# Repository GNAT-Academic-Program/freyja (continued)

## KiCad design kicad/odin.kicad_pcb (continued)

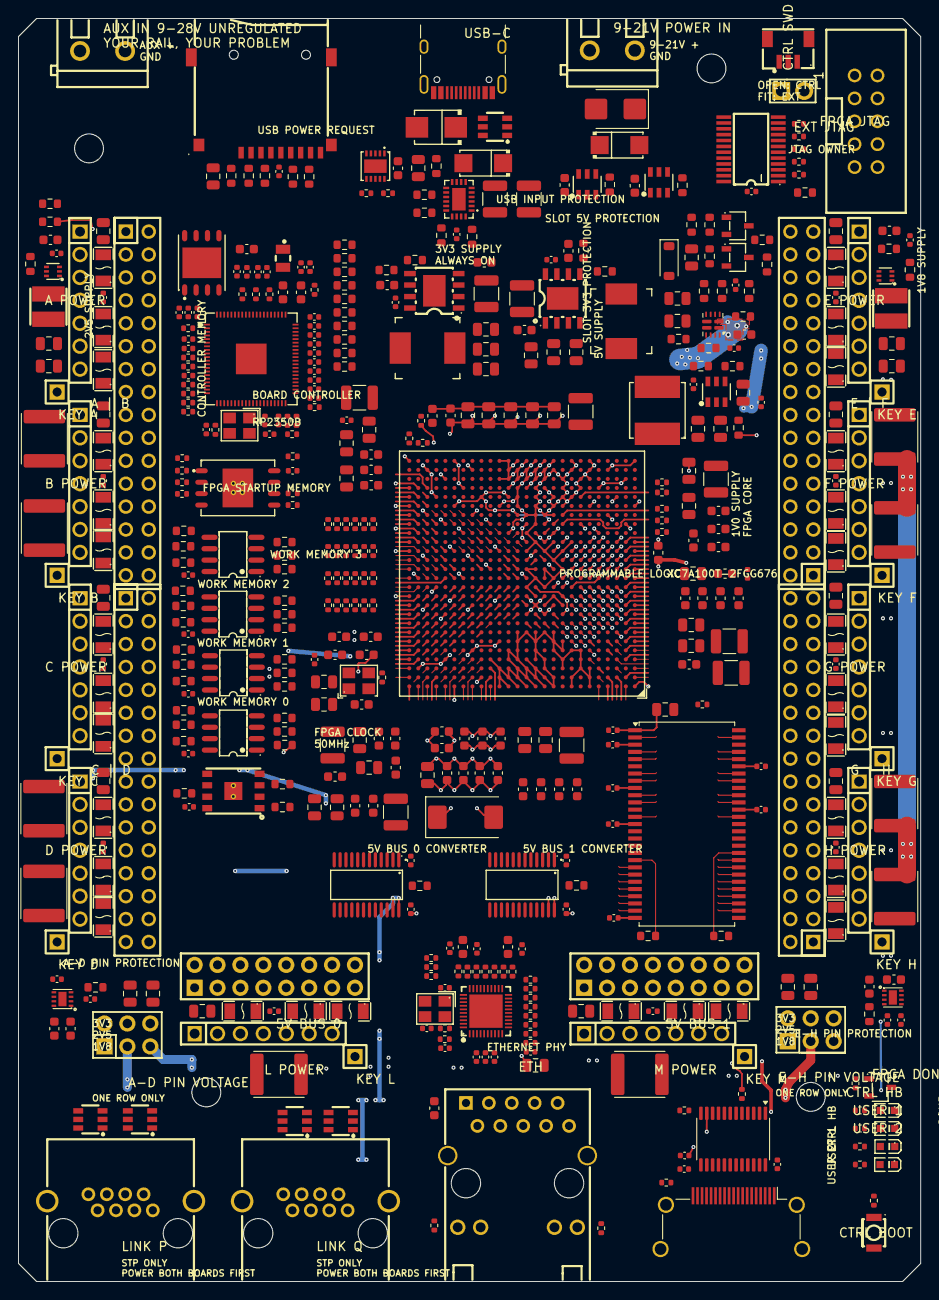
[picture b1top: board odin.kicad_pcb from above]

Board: 8 copper layers, 100.0 x 140.0 mm, 524 parts (0 on the bottom side), 498 nets.

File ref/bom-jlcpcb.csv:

Comment,Designator,Footprint,LCSC Part
100nF,"C111,C112,C113,C114,C115,C116,C117,C118,C119,C120,C121,C122,C123,C124,C125,C126,C127,C128,C129,C135,C136,C138,C139,C140,C141,C142,C144,C146,C148,C150,C152,C154,C156,C158,C160,C162,C188,C193,C200,C203,C225,C226,C227,C228,C229,C230,C232,C233,C234,C236,C238,C239,C240,C241,C246,C247,C248,C249,C250,C251,C252,C253,C254,C255,C256,C258,C259,C262,C263,C271,C274,C277,C278,C285,C286,C328",C_0402_1005Metric,C1525
4.7uF,"C130,C131,C132,C242,C268,C269",C_0603_1608Metric,C277476
15pF,"C133,C134",C_0402_1005Metric,
1uF 25V,C137,C_0603_1608Metric,C29936
10uF,"C143,C145,C147,C149,C151,C153,C155,C157,C159,C161,C235,C257,C260,C261,C279",C_0805_2012Metric,C15850
22uF,"C163,C164,C165,C166,C189,C190,C191,C195,C196,C197,C198,C199,C201,C202,C207,C211,C212,C265,C266",C_0805_2012Metric,C86816
10nF 25V,C184,C_0402_1005Metric,
10uF 50V,"C185,C186,C192,C267",C_1210_3225Metric,C77102
10uF 25V,C187,C_0805_2012Metric,C15850
1uF,"C218,C219,C220,C221,C237,C273,C276,C280,C281,C283",C_0603_1608Metric,C29936
100nF 50V,C243,C_0603_1608Metric,
18pF,"C244,C245",C_0402_1005Metric,
100nF 25V,C264,C_0402_1005Metric,C1525
1nF 50V,"C272,C275",C_0402_1005Metric,
220nF 50V,"C282,C284",C_0603_1608Metric,
330uF 6.3V T520V337M006ATE025,C301,CP_EIA-7343-31_Kemet-D,C136150
4.7uF 6.3V,"C302,C303,C304,C305,C306,C307,C320,C321,C322,C330,C331,C336,C337,C342,C343,C348,C349,C354,C355,C360,C361",C_0805_2012Metric,
0.47uF 6.3V,"C308,C309,C310,C311,C312,C313,C314,C315,C317,C318,C323,C324,C325,C326,C327,C332,C333,C334,C335,C338,C339,C340,C341,C344,C345,C346,C347,C350,C351,C352,C353,C356,C357,C358,C359,C362,C363,C364,C365",C_0603_1608Metric,
100uF 2.5V,C316,C_1210_3225Metric,
47uF 6.3V,"C319,C329,C366,C367,C368,C369,C394",C_1210_3225Metric,
F.0603.00025/P2-0603G1TS2-06T-002,"D1,D9,D10,D11",LED0603-RD_GREEN,C7496818
SS54,"D3,D4",SMA_L4.3-W2.6-LS5.2-RD,C22452
ESDA6V1BC6,D6,SOT-23-6_L2.9-W1.6-P0.95-LS2.8-BR,C495220
SMBJ12A,D7,SMB_L4.3-W3.6-LS5.3-RD,C19077565
SMBJ22A,D8,D_SMB,C151920
TPD4E1U06DBVR,"D20,D21,D22,D23",SOT-23-6_L2.9-W1.6-P0.95-LS2.8-BR_TPD4E1U06,C124691
1N4148W,D24,D_SOD-123,C81598
500mA,"F1,F3,F5,F7,F9,F11,F13,F15,F17,F19,F21,F23,F25,F27,F29,F31,F33,F35,F37,F39",F1206,C269115
1.1A,"F2,F6,F10,F14,F18,F22,F26,F30,F34,F38",F1206,C269119
1.1A 33V,"F4,F8,F12,F16,F20,F24,F28,F32,F36,F40",Fuse_TECHFUSE_SMD2018,C70150
120R 2A BLM18PG121SN1D,FB1,L_0603_1608Metric,C14709
USB-C,J1,USB_C_Receptacle_HRO_TYPE-C-31-M-12,C165948
FPGA JTAG,J2,IDC-TH_10P-P2.54_C5665,C5665
HC-PM254-8.5H-2x16PZ,"J3A,J3B,J5A,J5B",HDR-TH_32P-P2.54-V-F-R2-C16-S2.54,C22373921
2.54-2*8P female 8.5mm,"J7,J8",HDR-TH_16P-P2.54-V-F-R2-C8-S2.54,C30734
2.54-2*3P,"J19,J20",HDR-TH_6P-P2.54-V-M-R2-C3-S2.54-1,C65114
9-21V POWER IN,J50,CONN-TH_P5.00_KF301-5.0-2P,C474881
CTRL SWD,J51,CONN-SMD-3P-P1.00_BM03B-SRSS-TB-LF-SN,C160389
PZ254V-11-02P,J52,HDR-TH_2P-P2.54-V-M,C492401
B254N02-0B7P51-H85C32,"J53,J54,J55,J56,J57,J58,J62,J63,J64,J65",HDR-TH_7P-P2.54-V-F,C41426870
AUX IN 9-28V UNREGULATED,J68,CONN-TH_P5.00_KF301-5.0-2P,C474881
ETH,J70,RJ45-TH_HR911130A,C54408
LINK P,J71,RJ45-TH_R-RJ45R08P-B000,C386756
LINK Q,J72,RJ45-TH_R-RJ45R08P-B000,C386756
HDMI OUT,J73,HDMI_A_Amphenol_10029449-x01xLF_Horizontal,C427307
microSD,J74,TF-SMD_TF-01A-NPTH,C91145
3.3uH AOTA-B201610S3R3-101-T,L1,IND-SMD_L2.0-W1.6_AOTA-B201610S3R3-101-T,C42411119
10uH MWSA0603S-100MT,"L2,L3",IND-SMD_L7.0-W6.6_MWSA0603S,C132141
2.2uH SRN4018-2R2M,"L4,L5",IND-SMD_L4.0-W4.0_SNR4018,C913207
4.7uH SWPA6045S4R7MT,L7,IND-SMD_L6.0-W6.0_SWPA6045S,C78804
BOOMELE 2.54-1x40P-21mm; cut to 1P; hand/wave soldered,"MK65,MK66,MK67,MK68,MK69,MK70,MK71,MK72,MK76,MK77",HDR-TH_1P-P2.54-V-M-21MM-C51353,C51353
BSS138LT1G,"Q4,Q6,Q7",SOT-23-3_L2.9-W1.6-P1.90-LS2.8-BR,C82045
1k,"R1,R2,R3,R6,R9,R10,R12,R128,R129,R130,R132",R_0402_1005Metric,C11702
4.7k,"R4,R5,R98,R133,R135,R136,R137,R138,R139,R140,R141,R142,R143,R172,R203,R204",R_0402_1005Metric,C25900
330,R7,R_0402_1005Metric,
33,"R8,R14,R15,R16,R17,R18,R19,R20,R21,R22,R23,R24,R25,R26,R27,R28,R29,R30,R31,R32,R104,R105,R106,R107,R108,R109,R110,R111,R112,R113,R114,R115,R116,R117,R118,R119,R120,R121,R122,R123,R124,R125,R126,R127,R147,R208",R_0402_1005Metric,C25105
0,"R33,R146,R205",R_0402_1005Metric,
10k,"R34,R73,R96,R97,R152,R153,R154,R155,R156,R157,R158,R159,R160,R161,R169,R174,R175,R176,R177,R178,R179,R180,R181,R182,R183,R184,R185,R186,R187,R188,R189,R190,R191,R192,R193,R194,R195,R196,R197,R207",R_0603_1608Metric,
110k,R50,R_0603_1608Metric,
24.9k,R51,R_0603_1608Metric,
14.7k,R52,R_0603_1608Metric,
29.4k,"R54,R168",R_0603_1608Metric,
100k 0.1%,"R55,R57,R59",R_0603_1608Metric,C122538
24.9k 0.1%,R56,R_0603_1608Metric,C136967
43.2k 0.1%,R58,R_0603_1608Metric,C861404
31.6k 0.1%,R60,R_0603_1608Metric,C705766
102k 0.1%,R61,R_0603_1608Metric,C861068
49.9k 0.1%,R62,R_0603_1608Metric,C705780
3.09k 0.1%,R67,R_0603_1608Metric,C861371
10k 0.1%,R68,R_0603_1608Metric,C95204
100k,"R72,R81,R83,R91,R94,R162,R164,R166,R201",R_0603_1608Metric,
604,R74,R_0603_1608Metric,
1.15k,R75,R_0603_1608Metric,
16k,R82,R_0603_1608Metric,
47k,R84,R_0603_1608Metric,
1k,"R85,R86,R87,R88,R198,R199",R_0603_1608Metric,
2.49k 1%,R131,R_0402_1005Metric,
1.5k,R134,R_0402_1005Metric,
510,"R144,R145",R_0402_1005Metric,
100k,"R148,R149,R173",R_0402_1005Metric,C25741
75,R150,R_0402_1005Metric,
22,R151,R_0402_1005Metric,
36.5k,R163,R_0603_1608Metric,
23.2k,R165,R_0603_1608Metric,
56.2k,R167,R_0603_1608Metric,
27,"R170,R171",R_0402_1005Metric,
470k,R200,R_0603_1608Metric,
33k,R202,R_0603_1608Metric,
4.53k,R206,R_0402_1005Metric,
47,"R209,R210,R211,R212,R213",R_0402_1005Metric,
CTRL BOOT,SW1,KEY-SMD_B3U-1000PM,C231329
XC7A100T-2FGG676I,U1,FBGA-676_L27.0-W27.0-R26-C26-P1.00-BL,C1521803
APS6404L-SQN-SN,"U2,U3,U4,U5",SOIC-8_L4.9-W3.9-P1.27-LS6.0-BL,C5360304
W25Q256JVEIQ,U6,WSON-8_L8.0-W6.10-P1.27-BL-EP,C97522
RP2350B,U7,QFN-80_L10.0-W10.0-P0.40-TL-EP3.4,C42415655
W25Q32JVZP,U8,WSON-8_L6.0-W5.0-P1.27-BL-EP,C571260
SN74LVC8T245PWR,"U9,U10",TSSOP-24_L7.8-W4.4-P0.65-LS6.4-BL_1,C27643
LMR33630ADDAR,"U11,U12",ESOP-8_L4.9-W3.9-P1.27-LS6.0-TL-EP,C841384
TLV62569PDRLR,"U13,U14",SOT-563_L1.6-W1.2-P0.50-LS1.6-BL,C398364
TPS564201DDCR,U15,SOT-23-6_L2.9-W1.6-P0.95-LS2.8-BL,C464812
HUSB238_002DD,U18,DFN-10_L3.0-W3.0-P0.50-BL-EP2.5,C7471904
SN74CB3Q3384APWR,U20,TSSOP-24_L7.8-W4.4-P0.65-LS6.4-BL,C469874
TPS22950CDDCR,"U21,U22",SOT-23-6_L2.9-W1.6-P0.95-LS2.8-BL_3,C7587833
TPS22975DSGR,"U23,U24",WSON-8_L2.0-W2.0-P0.50-TL-EP,C524777
TPS25942ARVCR,U26,QFN-20_L4.0-W3.0-P0.5-BL-EP,C181295
RTL8211FDI-CG,U30,QFN-40_L5.0-W5.0-P0.40-BL-EP3.7,C692886
TPD12S016PWR,U31,TSSOP-24_4.4x7.8mm_P0.65mm,C201665
W9825G6KH-6,U32,TSOP-II-54_22.2x10.16mm_P0.8mm,C62246
MR25H10CDF,U33,DFN-8_L5.0-W6.0-P1.27-EP2.0-2VIA,C246234
TPS2121RUXR,U34,Texas_VQFN-HR-12_2x2.5mm_P0.5mm,C485916
25MHz 12pF,X3,CRYSTAL-SMD_4P-L3.2-W2.5-BL_X3225,C9006
50MHz CMOS,X4,OSC-SMD_4P-L3.2-W2.5-BL,C717684
12MHz ABM8-272-T3,Y1,CRYSTAL-SMD_4P-L3.2-W2.5-BL,C20625731

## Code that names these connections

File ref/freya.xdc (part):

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set_property BITSTREAM.GENERAL.COMPRESS TRUE [current_design]

# ---- BUS5V0
set_property -dict {PACKAGE_PIN U24 IOSTANDARD LVCMOS18} [get_ports {BUS5V0_DIR}]   ;# bank 13 IO_0_13
set_property -dict {PACKAGE_PIN V26 IOSTANDARD LVCMOS18} [get_ports {BUS5V0_IO0}]   ;# bank 13 IO_L2P_T0_13
set_property -dict {PACKAGE_PIN W26 IOSTANDARD LVCMOS18} [get_ports {BUS5V0_IO1}]   ;# bank 13 IO_L2N_T0_13
set_property -dict {PACKAGE_PIN AB26 IOSTANDARD LVCMOS18} [get_ports {BUS5V0_IO2}]   ;# bank 13 IO_L3P_T0_DQS_13
set_property -dict {PACKAGE_PIN AC26 IOSTANDARD LVCMOS18} [get_ports {BUS5V0_IO3}]   ;# bank 13 IO_L3N_T0_DQS_13
set_property -dict {PACKAGE_PIN U25 IOSTANDARD LVCMOS18} [get_ports {BUS5V0_IO4}]   ;# bank 13 IO_L1P_T0_13
set_property -dict {PACKAGE_PIN U26 IOSTANDARD LVCMOS18} [get_ports {BUS5V0_IO5}]   ;# bank 13 IO_L1N_T0_13
set_property -dict {PACKAGE_PIN W25 IOSTANDARD LVCMOS18} [get_ports {BUS5V0_IO6}]   ;# bank 13 IO_L4P_T0_13
set_property -dict {PACKAGE_PIN Y26 IOSTANDARD LVCMOS18} [get_ports {BUS5V0_IO7}]   ;# bank 13 IO_L4N_T0_13
set_property -dict {PACKAGE_PIN V23 IOSTANDARD LVCMOS18} [get_ports {BUS5V0_OE_N}]   ;# bank 13 IO_L10P_T1_13
# ---- BUS5V1
set_property -dict {PACKAGE_PIN U17 IOSTANDARD LVCMOS18} [get_ports {BUS5V1_DIR}]   ;# bank 13 IO_25_13
set_property -dict {PACKAGE_PIN AC24 IOSTANDARD LVCMOS18} [get_ports {BUS5V1_IO0}]   ;# bank 13 IO_L9N_T1_DQS_13
set_property -dict {PACKAGE_PIN AB24 IOSTANDARD LVCMOS18} [get_ports {BUS5V1_IO1}]   ;# bank 13 IO_L9P_T1_DQS_13
set_property -dict {PACKAGE_PIN AB25 IOSTANDARD LVCMOS18} [get_ports {BUS5V1_IO2}]   ;# bank 13 IO_L7N_T1_13
set_property -dict {PACKAGE_PIN Y25 IOSTANDARD LVCMOS18} [get_ports {BUS5V1_IO3}]   ;# bank 13 IO_L5P_T0_13
set_property -dict {PACKAGE_PIN AA25 IOSTANDARD LVCMOS18} [get_ports {BUS5V1_IO4}]   ;# bank 13 IO_L5N_T0_13
set_property -dict {PACKAGE_PIN V24 IOSTANDARD LVCMOS18} [get_ports {BUS5V1_IO5}]   ;# bank 13 IO_L6P_T0_13
set_property -dict {PACKAGE_PIN W24 IOSTANDARD LVCMOS18} [get_ports {BUS5V1_IO6}]   ;# bank 13 IO_L6N_T0_VREF_13
set_property -dict {PACKAGE_PIN AA24 IOSTANDARD LVCMOS18} [get_ports {BUS5V1_IO7}]   ;# bank 13 IO_L7P_T1_13
set_property -dict {PACKAGE_PIN W23 IOSTANDARD LVCMOS18} [get_ports {BUS5V1_OE_N}]   ;# bank 13 IO_L10N_T1_13
# ---- DBG
set_property -dict {PACKAGE_PIN N21 IOSTANDARD LVCMOS33} [get_ports {DBG_TCK}]   ;# bank 14 IO_L13P_T2_MRCC_14
set_property -dict {PACKAGE_PIN M20 IOSTANDARD LVCMOS33} [get_ports {DBG_TDI}]   ;# bank 14 IO_L8P_T1_D11_14
set_property -dict {PACKAGE_PIN L20 IOSTANDARD LVCMOS33} [get_ports {DBG_TDO}]   ;# bank 14 IO_L8N_T1_D12_14
set_property -dict {PACKAGE_PIN N22 IOSTANDARD LVCMOS33} [get_ports {DBG_TMS}]   ;# bank 14 IO_L13N_T2_MRCC_14
# ---- FLASH
set_property -dict {PACKAGE_PIN P18 IOSTANDARD LVCMOS33} [get_ports {FLASH_CS_B}]   ;# bank 14 IO_L6P_T0_FCS_B_14
set_property -dict {PACKAGE_PIN R14 IOSTANDARD LVCMOS33} [get_ports {FLASH_D0_MOSI}]   ;# bank 14 IO_L1P_T0_D00_MOSI_14
set_property -dict {PACKAGE_PIN R15 IOSTANDARD LVCMOS33} [get_ports {FLASH_D1_MISO}]   ;# bank 14 IO_L1N_T0_D01_DIN_14
set_property -dict {PACKAGE_PIN P14 IOSTANDARD LVCMOS33} [get_ports {FLASH_D2_WP}]   ;# bank 14 IO_L2P_T0_D02_14
set_property -dict {PACKAGE_PIN N14 IOSTANDARD LVCMOS33} [get_ports {FLASH_D3_HOLD}]   ;# bank 14 IO_L2N_T0_D03_14
# ---- HDMI
set_property -dict {PACKAGE_PIN B2 IOSTANDARD LVCMOS33} [get_ports {HDMI_CEC}]   ;# bank 35 IO_L19N_T3_VREF_35
set_property -dict {PACKAGE_PIN A2 IOSTANDARD TMDS_33} [get_ports {HDMI_CLK_N}]   ;# bank 35 IO_L20N_T3_35
set_property -dict {PACKAGE_PIN A3 IOSTANDARD TMDS_33} [get_ports {HDMI_CLK_P}]   ;# bank 35 IO_L20P_T3_35
set_property -dict {PACKAGE_PIN F2 IOSTANDARD LVCMOS33} [get_ports {HDMI_CT_HPD}]   ;# bank 35 IO_L22P_T3_35
set_property -dict {PACKAGE_PIN B1 IOSTANDARD TMDS_33} [get_ports {HDMI_D0_N}]   ;# bank 35 IO_L21N_T3_DQS_35
set_property -dict {PACKAGE_PIN C1 IOSTANDARD TMDS_33} [get_ports {HDMI_D0_P}]   ;# bank 35 IO_L21P_T3_DQS_35
set_property -dict {PACKAGE_PIN D1 IOSTANDARD TMDS_33} [get_ports {HDMI_D1_N}]   ;# bank 35 IO_L23N_T3_35
set_property -dict {PACKAGE_PIN E1 IOSTANDARD TMDS_33} [get_ports {HDMI_D1_P}]   ;# bank 35 IO_L23P_T3_35
set_property -dict {PACKAGE_PIN A5 IOSTANDARD TMDS_33} [get_ports {HDMI_D2_N}]   ;# bank 35 IO_L15N_T2_DQS_35
set_property -dict {PACKAGE_PIN B5 IOSTANDARD TMDS_33} [get_ports {HDMI_D2_P}]   ;# bank 35 IO_L15P_T2_DQS_35
set_property -dict {PACKAGE_PIN B4 IOSTANDARD LVCMOS33} [get_ports {HDMI_HPD}]   ;# bank 35 IO_L16P_T2_35
set_property -dict {PACKAGE_PIN E2 IOSTANDARD LVCMOS33} [get_ports {HDMI_LS_OE}]   ;# bank 35 IO_L22N_T3_35
set_property -dict {PACKAGE_PIN A4 IOSTANDARD LVCMOS33} [get_ports {HDMI_SCL}]   ;# bank 35 IO_L16N_T2_35
set_property -dict {PACKAGE_PIN F4 IOSTANDARD LVCMOS33} [get_ports {HDMI_SDA}]   ;# bank 35 IO_L11N_T1_SRCC_35
# ---- LINK
set_property -dict {PACKAGE_PIN C18 IOSTANDARD LVDS_25} [get_ports {LINK_P_RXC_N}]   ;# bank 16 IO_L12N_T1_MRCC_16
set_property DIFF_TERM TRUE [get_ports {LINK_P_RXC_N}]
set_property -dict {PACKAGE_PIN D18 IOSTANDARD LVDS_25} [get_ports {LINK_P_RXC_P}]   ;# bank 16 IO_L12P_T1_MRCC_16
set_property DIFF_TERM TRUE [get_ports {LINK_P_RXC_P}]
set_property -dict {PACKAGE_PIN A18 IOSTANDARD LVDS_25} [get_ports {LINK_P_RXD_N}]   ;# bank 16 IO_L9N_T1_DQS_16
set_property DIFF_TERM TRUE [get_ports {LINK_P_RXD_N}]
set_property -dict {PACKAGE_PIN A17 IOSTANDARD LVDS_25} [get_ports {LINK_P_RXD_P}]   ;# bank 16 IO_L9P_T1_DQS_16
set_property DIFF_TERM TRUE [get_ports {LINK_P_RXD_P}]
set_property -dict {PACKAGE_PIN B26 IOSTANDARD LVDS_25} [get_ports {LINK_P_TXC_N}]   ;# bank 16 IO_L22N_T3_16
set_property -dict {PACKAGE_PIN C26 IOSTANDARD LVDS_25} [get_ports {LINK_P_TXC_P}]   ;# bank 16 IO_L22P_T3_16
set_property -dict {PACKAGE_PIN A24 IOSTANDARD LVDS_25} [get_ports {LINK_P_TXD_N}]   ;# bank 16 IO_L21N_T3_DQS_16
set_property -dict {PACKAGE_PIN A23 IOSTANDARD LVDS_25} [get_ports {LINK_P_TXD_P}]   ;# bank 16 IO_L21P_T3_DQS_16
set_property -dict {PACKAGE_PIN D20 IOSTANDARD LVDS_25} [get_ports {LINK_Q_RXC_N}]   ;# bank 16 IO_L14N_T2_SRCC_16
set_property DIFF_TERM TRUE [get_ports {LINK_Q_RXC_N}]
set_property -dict {PACKAGE_PIN E20 IOSTANDARD LVDS_25} [get_ports {LINK_Q_RXC_P}]   ;# bank 16 IO_L14P_T2_SRCC_16
set_property DIFF_TERM TRUE [get_ports {LINK_Q_RXC_P}]
set_property -dict {PACKAGE_PIN A20 IOSTANDARD LVDS_25} [get_ports {LINK_Q_RXD_N}]   ;# bank 16 IO_L15N_T2_DQS_16
set_property DIFF_TERM TRUE [get_ports {LINK_Q_RXD_N}]
set_property -dict {PACKAGE_PIN B20 IOSTANDARD LVDS_25} [get_ports {LINK_Q_RXD_P}]   ;# bank 16 IO_L15P_T2_DQS_16
set_property DIFF_TERM TRUE [get_ports {LINK_Q_RXD_P}]
set_property -dict {PACKAGE_PIN A25 IOSTANDARD LVDS_25} [get_ports {LINK_Q_TXC_N}]   ;# bank 16 IO_L20N_T3_16
set_property -dict {PACKAGE_PIN B25 IOSTANDARD LVDS_25} [get_ports {LINK_Q_TXC_P}]   ;# bank 16 IO_L20P_T3_16
set_property -dict {PACKAGE_PIN A22 IOSTANDARD LVDS_25} [get_ports {LINK_Q_TXD_N}]   ;# bank 16 IO_L17N_T2_16
set_property -dict {PACKAGE_PIN B22 IOSTANDARD LVDS_25} [get_ports {LINK_Q_TXD_P}]   ;# bank 16 IO_L17P_T2_16
# ---- MRAM
set_property -dict {PACKAGE_PIN K25 IOSTANDARD LVCMOS33} [get_ports {MRAM_CS}]   ;# bank 14 IO_L7P_T1_D09_14
set_property -dict {PACKAGE_PIN K26 IOSTANDARD LVCMOS33} [get_ports {MRAM_SCK}]   ;# bank 14 IO_L7N_T1_D10_14
set_property -dict {PACKAGE_PIN L24 IOSTANDARD LVCMOS33} [get_ports {MRAM_SI}]   ;# bank 14 IO_L9P_T1_DQS_14
set_property -dict {PACKAGE_PIN L25 IOSTANDARD LVCMOS33} [get_ports {MRAM_SO}]   ;# bank 14 IO_L9N_T1_DQS_D13_14
# ---- PHY
set_property -dict {PACKAGE_PIN G2 IOSTANDARD LVCMOS33} [get_ports {PHY_INT_N}]   ;# bank 35 IO_L24P_T3_35
set_property -dict {PACKAGE_PIN C17 IOSTANDARD LVCMOS25} [get_ports {PHY_MDC}]   ;# bank 16 IO_L7P_T1_16
set_property -dict {PACKAGE_PIN B17 IOSTANDARD LVCMOS25} [get_ports {PHY_MDIO}]   ;# bank 16 IO_L7N_T1_16
set_property -dict {PACKAGE_PIN G1 IOSTANDARD LVCMOS33} [get_ports {PHY_RESET_N}]   ;# bank 35 IO_L24N_T3_35
set_property -dict {PACKAGE_PIN D19 IOSTANDARD LVCMOS25} [get_ports {PHY_RXC}]   ;# bank 16 IO_L13P_T2_MRCC_16
set_property -dict {PACKAGE_PIN C19 IOSTANDARD LVCMOS25} [get_ports {PHY_RXD0}]   ;# bank 16 IO_L13N_T2_MRCC_16
set_property -dict {PACKAGE_PIN H17 IOSTANDARD LVCMOS25} [get_ports {PHY_RXD1}]   ;# bank 16 IO_0_16
set_property -dict {PACKAGE_PIN E22 IOSTANDARD LVCMOS25} [get_ports {PHY_RXD2}]   ;# bank 16 IO_25_16
set_property -dict {PACKAGE_PIN B19 IOSTANDARD LVCMOS25} [get_ports {PHY_RXD3}]   ;# bank 16 IO_L10P_T1_16
set_property -dict {PACKAGE_PIN A19 IOSTANDARD LVCMOS25} [get_ports {PHY_RX_CTL}]   ;# bank 16 IO_L10N_T1_16
set_property -dict {PACKAGE_PIN C24 IOSTANDARD LVCMOS25} [get_ports {PHY_TXC}]   ;# bank 16 IO_L23P_T3_16
set_property SLEW FAST [get_ports {PHY_TXC}]
set_property -dict {PACKAGE_PIN B24 IOSTANDARD LVCMOS25} [get_ports {PHY_TXD0}]   ;# bank 16 IO_L23N_T3_16
set_property SLEW FAST [get_ports {PHY_TXD0}]
set_property -dict {PACKAGE_PIN C22 IOSTANDARD LVCMOS25} [get_ports {PHY_TXD1}]   ;# bank 16 IO_L19P_T3_16
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
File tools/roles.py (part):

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# ----------------------------------------------------------------- nets
# Notes appended to the derived line of any R/C on that net.
NET = {
    'CFG_M0': 'mode pin M0 = 1: master SPI boot (UG470 Table 2-4, at most 1 k)',
    'CFG_M1': 'mode pin M1 = 0: master SPI boot (UG470 Table 2-4)',
    'CFG_M2': 'mode pin M2 = 0: master SPI boot (UG470 Table 2-4)',
    'CFG_PROG_B': 'keeps PROGRAM_B released; pulling it low restarts configuration',
    'CFG_INIT_B': 'keeps INIT_B released; it goes low on a configuration error',
    'PUDC_B': 'PUDC_B high: no I/O pull-ups during configuration, the external resistors set every line (UG470)',
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    'MRAM_HOLD': 'hold released: transfers never pause',
    'SDRAM_CS_N': 'keeps the SDRAM deselected until a design drives CS',
    'SDRAM_CKE': 'holds the SDRAM clock disabled (power-down) until a design drives CKE',
    'PHY_TXC_U30': 'filters TXC at U30\'s pin, about 4 mm from it: not source termination (gateware/rgmii1000)',
    'PHY_TX_CTL_U30': 'filters TX_CTL at U30\'s pin, about 4 mm from it: not source termination (gateware/rgmii1000)',
    'PHY_TXD0_U30': 'filters TXD0 at U30\'s pin, about 4 mm from it: not source termination (gateware/rgmii1000)',
    'PHY_TXD1_U30': 'filters TXD1 at U30\'s pin, about 4 mm from it: not source termination (gateware/rgmii1000)',
    'PHY_TXD2_U30': 'filters TXD2 at U30\'s pin, about 4 mm from it: not source termination (gateware/rgmii1000)',
    'PHY_TXD3_U30': 'filters TXD3 at U30\'s pin, about 4 mm from it: not source termination (gateware/rgmii1000)',
    'PHY_RSET': 'sets U30\'s transmit bias current (2.49 k 1 %, [verify] ref/network.md)',
    'PHY_1V0': 'U30\'s internal 1.0 V LDO output; feeds only its own core pins',
    'PHY_RESET_N': 'holds U30 in reset until the FPGA drives it (Table 53 note 5)',
    'PHY_INT_N': 'U30\'s open-drain interrupt (Table 4)',
    'PHY_MDIO': 'MDIO idle-high pull-up, 1.5 k (section 7.11.2)',
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        'The FPGA core supply: up to 4 A at 1.0 V from +5V, the heaviest rail '
        'on the board. Enabled by the board controller (EN_1V0) once +5V is '
        'settled above its 4.5 V minimum; firmware watches the rail through '
        'MON_1V0 (the part has no power-good pin). The feedback resistors '
        'set 1.0 V; the bootstrap capacitor feeds its high-side driver.',
    'extension power protection control':
        'Shared control for the four protected extension supplies (U21-U24). '
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    'rail monitors':
        'Lets the board controller measure every supply. Each rail goes to '
        'one of its eight analog inputs (ADC), which read 0-3.3 V. Rails at '
        'or below 3.3 V go through a 1 k resistor that protects the pin; VSYS '
        'and +5V are higher, so two resistors divide them down first. A 100 '
        'nF capacitor on each input steadies the reading. MON_1V8 reads +1V8 '
        'itself, the FPGA\'s VCCAUX behind the bead, so an open bead shows; '
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        'Standard 2x5 JTAG header for an external FPGA programmer (Xilinx/AMD '
        'cable or similar). Fit J52 first.',
    'board status LEDs':
        'Three green LEDs on board controller GPIO35-37, lit by driving the '
        'pin low: CTRL HB blinks while the board controller firmware is '
        'alive; USER 1 and USER 2 are for software. Each has a 1 k '
        'current-limiting resistor from +3V3. Rules: ref/status-leds.md.',
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    'VBUS5_SS': 'sets how fast U34 ramps the +5V rail, about 780 V/s',
    'VBUS5_ST': 'U34 status to the board controller: low when U11 feeds +5V',
    'PD_REQ_9V': 'raised by the board controller while it asks U18 for 9 V; holds the +5V mux on U11 through D24/Q6',
    'PD_SDA': 'I2C1 data to U18 (GPIO14), 4.7k pull-up to +3V3',
    'PD_SCL': 'I2C1 clock to U18 (GPIO31), 4.7k pull-up to +3V3',
    'PD_VSET': 'U18 voltage strap: 0 ohm = ask for 5 V on its own (HUSB238 Table 5)',
    'PD_ISET': 'U18 current strap: 4.53k = 1.5 A (HUSB238 Table 6)',
    'USB_DP_MCU': 'USB D+ at the controller, after its 27 ohm series resistor',
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
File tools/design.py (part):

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    # controller U18 is on I2C1 (SDA 14, SCL 31) since 2026-10-30. The 9 V
    # request is still one line, PD_REQ_9V (item 37): firmware raises it
    # (it drives the U34 hold, Q6) while it asks U18 for 9 V over I2C. U11
    # and U14 have no enable any more (item 34); GPIO21 reads which source
    # feeds +5V (item 35). The three status LEDs are plain GPIOs (35-37);
    # the I2C expander that used to carry them is gone (owner, 2026-10-30:
    # an extended part plus passives for four lines the RP2350 has spare).
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          8:'EXT_EN', 34:'EXT_FAULT',
          35:'LED_HEARTBEAT_N', 36:'LED_USER1_N', 37:'LED_USER2_N'}
    for g, n in gp.items(): sup[f'GPIO{g}'] = n
    # ADC0-7 (GPIO40-47): MON_1V8 reads +1V8 itself, VCCAUX behind FB1, not
    # the regulator side of the bead (item 50); the two jumpered domains are
    # measured so firmware knows the J19/J20 setting.
    for a, n in enumerate(['MON_VSYS','MON_5V','MON_3V3','MON_2V5','MON_1V8','MON_1V0',
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    d.C('4.7uF', '+1V1', GND, C0603)           # C7, the regulator output
    d.R('33', V33, 'SUP_VREG_AVDD', R0402)     # R3, RC filter for the
    d.C('4.7uF', 'SUP_VREG_AVDD', GND, C0603)  # C9, analogue supply
    d.L('3.3uH', 'SUP_LX', '+1V1')             # L1, mandated by RP-008280; pin 2 is the
    # end with the white polarity dot on the imported footprint (the dot sits
    # at pad 2), and RP2350 datasheet Figure 26 puts that dot at the +1V1 pad
    d.group('crystal (RP-008280 s4)')
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    # the crystal is not over-driven.
    d.add('Y1', 'Device:Crystal_GND24', '12MHz ABM8-272-T3', XTAL,
          {'1': 'SUP_XIN', '3': 'SUP_XTAL_OUT', 'G': GND}, 'C20625731')
    d.R('1k', 'SUP_XOUT', 'SUP_XTAL_OUT', R0402)   # R2, drive-level damping
    d.C('15pF', 'SUP_XIN', GND); d.C('15pF', 'SUP_XTAL_OUT', GND)
    d.group('RUN')
    d.R('1k', V33, 'SUP_RUN'); d.C('100nF', 'SUP_RUN', GND)
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    # 4.53k (Table 6: 1.5 A), so the board asks for 5 V at 1.5 A before,
    # without and in spite of the controller; the controller asks for 9 V
    # over I2C (PDO_SELECT = 9 V, GO_COMMAND; register map rev 2.0) while
    # it raises PD_REQ_9V for the U34 hold. Unlike the CH224K's CFG pins,
    # I2C can select any PDO the charger offers: the 9 V ceiling is no
    # longer by construction. Firmware must never select above 9 V; U26's
    # 10.07 V OVP opens the path above that and D7 (13.3-14.7 V breakdown)
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        d.R('33', a, b)
    # ---- real isolation between the supervisor's JTAG and the FPGA's
    # J2 exists for the case where the board is broken, which is exactly when a
    # firmware contract ("the supervisor promises to tri-state GPIO0-3") is
    # worth least. So the separation is a FET bus switch, and the control is a
    # jumper a human moves, not a GPIO -- there is no spare GPIO, and more to
    # the point a debug path should not depend on the thing being debugged.
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    # with an adjustable rise time (CT), thermal shutdown and quick output
    # discharge (230 ohm to GND while off). Unlike the TPS22953 it has no
    # PG, no SNS and no reverse current blocking: EXT_FAULT is U21, U22
    # and U26 only, and a slot that back-feeds its PIN V pin while EXT_EN
    # is low sees the switch's body diode (ref/extension-ux.md says so).
    # No programmable current limit either: the 500 mA PINV branch PTC in
    # every slot is the overload protection. ON VIH 1.05-1.2 V, so EXT_EN
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          'EasyEDA:CONN-TH_P5.00_KF301-5.0-2P',
          {'1': 'AUX_RAIL', '2': GND}, 'C474881')

    # Cathodes on RP2350 GPIO35-37, anodes through 1k from +3V3: a GPIO
    # driven low lights the LED, about 1.2 mA each. Dark at power-on and in
    # reset, when the pads are high-impedance with a weak pull-down and the
    # anode resistor alone sets the current (none through a dark LED).
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
    d.group('PHY straps and LEDs')
    # PHYRSTB: 3.3 V input, Table 58 (VIH 2.0 V), driven from bank 35. The
    # 1k pull-down holds it low while the FPGA pin floats (PUDC_B is high:
    # no configuration pull-ups) and until +2V5 is up (Table 53 note 5 case
    # II). Section 7.17: after release wait >= 72 ms before MDIO.
    d.R('1k', 'PHY_RESET_N', GND)
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    # must be high and track VDD within 200 mV, CLK low, and SI/SO/SIO[3:0]
    # low; then a reset-enable/reset pair. The resistors sit on the memory
    # side of the 33 ohm series resistors (the _MEM nets), 10k each: against
    # a floating FPGA pin (PUDC_B high, 10 uA leakage) that is 0.1 V, far
    # below the 0.4 V VIL; CE# follows VDD through the pull-up with no FPGA
    # drive. 20 pull-downs cost 3.6 mA when every line is high. The 150 us
    # wait and the reset sequence are the memory controller's job
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
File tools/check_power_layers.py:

#!/usr/bin/env python3
"""Power rails stay on the power layer.

Fails when a power net has a copper run on a signal layer (F.Cu, B.Cu and the
inner signal layers) longer than LIMIT_MM. A run is the copper between two vias
or pads of the net: track segments of one net on one layer joined end to end,
ending wherever a segment end sits on a via or a pad of that net (or is left
open). Where a run branches, its length is the longest way through it. Chains of
short pin-to-via stubs that only meet at pads or vias are therefore separate
runs; a rail drawn as a trace is one long run.

A filled zone island of a power net on a signal layer counts whole, with the
longer side of its bounding box: a pour is rail copper wherever its vias are.

Ground is not a rail here and is not checked. The power layer (In3) and the
ground planes are not signal layers.

Exceptions are listed by name only, net and layer, in ALLOWED.

Usage: tools/check_power_layers.py [board]     exit 1 on any failure
"""
import collections, re, sys
import pcbnew

LIMIT_MM = 10.0
ALLOWED = {
    ('AUX_RAIL', 'B.Cu'): 'AUX trunk in its reserved lane beside the east 1.8 V strip',
    ('+1V0', 'In2_signal'): 'core regulator sense line from ball V10 (no load current)',
}
POWER_CLASSES = {'PWR_3A', 'AUX_5A', 'EXT_2A'}
POWER_NAME = re.compile(r'^(\+.*|VBUS|VSYS|VIN_EXT|AUX_RAIL|PHY_1V0|VCCIO_\d(_EXT)?|SLOT_[A-Z]_(5V|3V3|AUX|PIN_VOLTAGE))$')


def is_power(net):
    name = net.GetNetname()
    if not name or name == 'GND':
        return False
    return bool(POWER_NAME.match(name)) or bool(POWER_CLASSES & set(net.GetNetClassName().split(',')))


def main():
    path = sys.argv[1] if len(sys.argv) > 1 else 'kicad/odin.kicad_pcb'
    b = pcbnew.LoadBoard(path)
    signal = [l for l in b.GetEnabledLayers().CuStack()
              if not re.search(r'GND|power', b.GetLayerName(l), re.I)]
    power = {n.GetNetname() for n in b.GetNetInfo().NetsByNetcode().values() if is_power(n)}

    chains = []                                   # (net, layer name, length, widths, where, what)
    vias = collections.defaultdict(list)
    for t in b.GetTracks():
        if t.Type() == pcbnew.PCB_VIA_T and t.GetNetname() in power:
            vias[t.GetNetname()].append((t.GetPosition(), t.GetWidth(pcbnew.F_Cu) // 2))
    pads = collections.defaultdict(list)
    for f in b.GetFootprints():
        for p in f.Pads():
            if p.GetNetname() in power:
                pads[p.GetNetname()].append(p)
    for layer in signal:
        lname = b.GetLayerName(layer)
        tracks = collections.defaultdict(list)
        for t in b.GetTracks():
            if t.Type() != pcbnew.PCB_VIA_T and t.GetLayer() == layer and t.GetNetname() in power:
                tracks[t.GetNetname()].append(t)
        for net, ts in sorted(tracks.items()):
            # graph: nodes are segment end points, edges are segments
            edges = collections.defaultdict(list)          # node -> [(other node, length mm, segment index)]
            for i, t in enumerate(ts):
                a, c = (t.GetStart().x, t.GetStart().y), (t.GetEnd().x, t.GetEnd().y)
                edges[a].append((c, t.GetLength() / 1e6, i)); edges[c].append((a, t.GetLength() / 1e6, i))

            def terminal(n):
                pt = pcbnew.VECTOR2I(n[0], n[1])
                if any((pt.x - v.x) ** 2 + (pt.y - v.y) ** 2 <= r * r for v, r in vias[net]):
                    return True
                return any(p.IsOnLayer(layer) and p.HitTest(pt) for p in pads[net])
            term = {n: terminal(n) for n in edges}
            seen = set()
            for i0, t0 in enumerate(ts):
                if i0 in seen:
                    continue
                # one run: the segments reachable from this one without passing through a via or pad
                run, nodes, todo = set(), set(), [i0]
                while todo:
                    i = todo.pop()
                    if i in run:
                        continue
                    run.add(i); t = ts[i]
                    for n in ((t.GetStart().x, t.GetStart().y), (t.GetEnd().x, t.GetEnd().y)):
                        nodes.add(n)
                        if not term[n]:
                            todo += [j for _, _, j in edges[n] if j not in run]
                seen |= run
                best = (0.0, None, None)                   # longest way through the run
                for src in nodes:
                    dist = {src: 0.0}; todo = [src]
                    while todo:
                        n = todo.pop()
                        if n != src and term[n]:
                            continue
                        for m, l, j in edges[n]:
                            if j in run and dist[n] + l < dist.get(m, 1e18):
                                dist[m] = dist[n] + l; todo.append(m)
                    far = max(dist, key=dist.get)
                    if dist[far] > best[0]:
                        best = (dist[far], src, far)
                widths = sorted({ts[i].GetWidth() / 1e6 for i in run})
                where = '(%.1f, %.1f) to (%.1f, %.1f)' % (best[1][0] / 1e6, best[1][1] / 1e6, best[2][0] / 1e6, best[2][1] / 1e6)
                chains.append((net, lname, best[0], widths, where, f'run of {len(run)} segment' + ('s' if len(run) > 1 else '')))
        for z in b.Zones():
            if z.GetIsRuleArea() or z.GetNetname() not in power or not z.GetLayerSet().Contains(layer):
                continue
            fill = z.GetFilledPolysList(layer)
            for i in range(fill.OutlineCount()):
                bb = fill.Outline(i).BBox()
                chains.append((z.GetNetname(), lname, max(bb.GetWidth(), bb.GetHeight()) / 1e6,
                               [round(min(bb.GetWidth(), bb.GetHeight()) / 1e6, 1)],
                               'x %.1f-%.1f y %.1f-%.1f' % (bb.GetX() / 1e6, bb.GetRight() / 1e6, bb.GetY() / 1e6, bb.GetBottom() / 1e6),
                               f"zone '{z.GetZoneName() or 'unnamed zone'}'"))

    long_ = sorted((c for c in chains if c[2] > LIMIT_MM), key=lambda c: -c[2])
    fails = [c for c in long_ if (c[0], c[1]) not in ALLOWED]
    for c in long_:
        tag = 'allowed' if (c[0], c[1]) in ALLOWED else 'FAIL   '
        why = f"  [{ALLOWED[(c[0], c[1])]}]" if tag == 'allowed' else ''
        print(f"{tag} {c[0]:10s} {c[1]:11s} {c[2]:6.1f} mm  width {'/'.join(f'{w:g}' for w in c[3])} mm  {c[4]}  {c[5]}{why}")
    print(f'power on signal layers: {len(fails)} runs over {LIMIT_MM:g} mm'
          f' ({len(long_) - len(fails)} allowed by name), {len(power)} power nets, layers '
          + ' '.join(b.GetLayerName(l) for l in signal))
    sys.exit(1 if fails else 0)


if __name__ == '__main__':
    main()
